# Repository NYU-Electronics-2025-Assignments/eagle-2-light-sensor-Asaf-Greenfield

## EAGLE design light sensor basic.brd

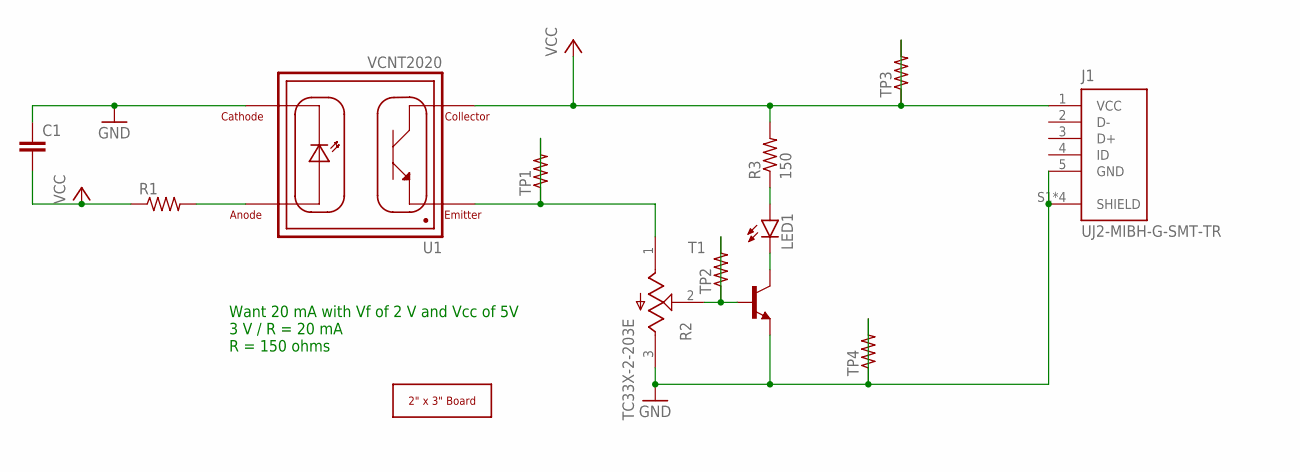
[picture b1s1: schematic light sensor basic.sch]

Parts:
C1: C-EUC1206; C1206
J1: UJ2-MIBH-G-SMT-TR; CUI_UJ2-MIBH-G-SMT-TR
LED1: LEDSML0805; SML0805
R1: R-US_R1206; R1206
R2: TC33X-2-203E; TRIM_TC33X-2-203E
R3: 150; R0805
T1: -NPN-SOT23-EBC; SOT23-EBC
TP1, TP2, TP3, TP4: R-US_R1206; R1206
U1: VCNT2020; XDCR_VCNT2020
U$1: 2X3_BOARD_V2

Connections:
GND: C1.1, J1.5 (GND), J1.S1 (SHIELD), J1.S2 (SHIELD), J1.S3 (SHIELD), J1.S4 (SHIELD), R2.3 (CW), T1.E, TP4.1, TP4.2, U1.4 (CATHODE)
unnamed: R1.2, U1.3 (ANODE)
unnamed: R2.2 (W), T1.B, TP2.1, TP2.2
unnamed: LED1.A, R3.1
unnamed: LED1.C, T1.C
TP1: R2.1 (CCW), TP1.1, TP1.2, U1.1 (EMITTER)
VCC: C1.2, J1.1 (VCC), R1.1, R3.2, TP3.1, TP3.2, U1.2 (COLLECTOR)

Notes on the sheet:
Want 20 mA with Vf of 2 V and Vcc of 5V 3 V / R = 20 mA R = 150 ohms

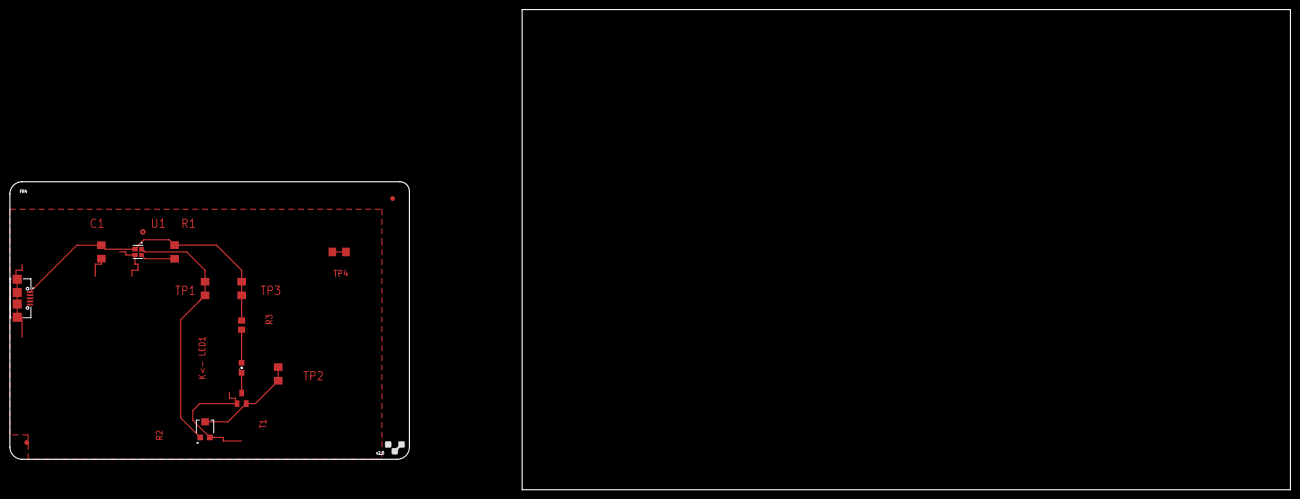
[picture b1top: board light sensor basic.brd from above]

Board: 2 copper layers, 83.2 x 57.8 mm, 13 parts (0 on the bottom side), 7 nets.

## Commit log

2025-03-01 Eagle 2
    Eagle 2
